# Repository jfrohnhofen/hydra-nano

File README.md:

# hydra nano

**hydra nano** is an open-source, ultra-compact 8-channel sACN (E1.31) lighting output controller. Powered by a Raspberry Pi Pico (RP2040) and a WIZnet W5500 SPI Ethernet module, it drives WS2812B addressable LED strings (via RP2040 PIO state machines) or high-frequency hardware PWM dimmers, configurable via a web interface.

---

## Features

- **8 Independent Output Channels**, each supporting one of the following modes:
  - **WS2812B Pixel Mode**: Up to 1,000 pixels per channel.
  - **WS2812B Uniform Fill Mode**: Controls an entire strip with a single DMX RGB slot triplet.
  - **PWM Dimming**: High-frequency PWM for MOSFET-switched single-color fixtures.
- **sACN Protocol Support**:
  - Listens on multicast and unicast UDP port `5568`.
  - Configurable stream loss behavior per channel: **Hold**, **Blackout**, or timed **Fade**.
- **Robust Networking & Zero-Conf Discovery**:
  - Hardware TCP/IP offload via WIZnet W5500 10/100 Mbps Ethernet.
  - Automatic DHCP with auto-retry.
  - Deterministic fallback link-local IPv4 (`169.254.x.y`) derived from hardware UID.
  - mDNS announcement (`<hostname>.local`, `_http._tcp`, `_hydra_nano._tcp`) and ICMP ping support.
- **Embedded Web Management Server**:
  - Simple responsive web UI on port 80 for live universe stream monitoring, network setup, channel configuration, and interactive test pattern generation.
- **Code-Defined Hardware & Enclosure**:
  - Schematic and netlist defined in atopile code ([`pcb/main.ato`](pcb/main.ato)).
  - Level-shifted outputs (3.3V to 5V) with solder bypass jumpers.
  - Snap-fit 3D CAD enclosure models ([Onshape](https://cad.onshape.com/documents/83539edf775ddacd0b6ac004/w/c1c705bfbe98832503cfb8b5/e/50ee4a9a96b406c057eff376)) with label generator.

---

## Hardware Architecture

### Channel & GPIO Mapping

The 8 physical outputs are ordered West-to-East across the board headers:

| Channel | Label | RP2040 GPIO | PWM Slice / PIO | Level Shifter | Bypass Jumper | Output Connector |
| :---: | :---: | :---: | :---: | :---: | :---: | :---: |
| **Ch 1** | OUT 1 | `GP15` | PWM Slice 7 B / PIO0 SM0 | Shifter `A1` $\rightarrow$ `B1` | `SJ1` | IDC 6-Pin #1 Pin 4 |
| **Ch 2** | OUT 2 | `GP14` | PWM Slice 7 A / PIO0 SM1 | Shifter `A2` $\rightarrow$ `B2` | `SJ2` | IDC 6-Pin #1 Pin 1 |
| **Ch 3** | OUT 3 | `GP13` | PWM Slice 6 B / PIO0 SM2 | Shifter `A3` $\rightarrow$ `B3` | `SJ3` | IDC 10-Pin Pin 7 |
| **Ch 4** | OUT 4 | `GP12` | PWM Slice 6 A / PIO0 SM3 | Shifter `A4` $\rightarrow$ `B4` | `SJ4` | IDC 10-Pin Pin 5 |
| **Ch 5** | OUT 5 | `GP11` | PWM Slice 5 B / PIO1 SM0 | Shifter `A5` $\rightarrow$ `B5` | `SJ5` | IDC 10-Pin Pin 3 |
| **Ch 6** | OUT 6 | `GP10` | PWM Slice 5 A / PIO1 SM1 | Shifter `A6` $\rightarrow$ `B6` | `SJ6` | IDC 10-Pin Pin 1 |
| **Ch 7** | OUT 7 | `GP9` | PWM Slice 4 B / PIO1 SM2 | Shifter `A7` $\rightarrow$ `B7` | `SJ7` | IDC 6-Pin #2 Pin 4 |
| **Ch 8** | OUT 8 | `GP8` | PWM Slice 4 A / PIO1 SM3 | Shifter `A8` $\rightarrow$ `B8` | `SJ8` | IDC 6-Pin #2 Pin 1 |

---

### W5500 Ethernet SPI Wiring

The W5500 module is connected to RP2040 hardware `SPI0`:

| Signal | Pico GPIO | Pico Pin | W5500 Pin | Function |
| :--- | :---: | :---: | :---: | :--- |
| **MISO** | `GP0` | Pin 1 | Pin 12 | SPI0 RX / Master In Slave Out |
| **RSTn** | `GP1` | Pin 2 | Pin 11 | Active-low hardware reset |
| **SCK** | `GP2` | Pin 4 | Pin 4 | SPI0 Clock |
| **MOSI** | `GP3` | Pin 5 | Pin 3 | SPI0 TX / Master Out Slave In |
| **INTn / IRQ**| `GP4` | Pin 6 | Pin 6 | Active-low interrupt line |
| **CSn** | `GP5` | Pin 7 | Pin 5 | Active-low SPI Chip Select |

---

### IDC Headers & Connectors

Outputs are distributed via standard 2.54 mm pitch right-angle shrouded box headers:

- **IDC 6-Pin Header #1**:
  - Pin 1: `Ch 2` (GP14) | Pin 2: `GND` | Pin 3: `5V`
  - Pin 4: `Ch 1` (GP15) | Pin 5: `GND` | Pin 6: `5V`
- **IDC 10-Pin Header**:
  - Odd pins (signals/power): Pin 1: `Ch 6` (GP10), Pin 3: `Ch 5` (GP11), Pin 5: `Ch 4` (GP12), Pin 7: `Ch 3` (GP13), Pin 9: `5V`
  - Even pins: Dedicated ground lines (Pins 2, 4, 6, 8, 10: `GND`)
- **IDC 6-Pin Header #2**:
  - Pin 1: `Ch 8` (GP8) | Pin 2: `GND` | Pin 3: `5V`
  - Pin 4: `Ch 7` (GP9) | Pin 5: `GND` | Pin 6: `5V`

---

## Firmware

The firmware is written in async Rust using the **Embassy** framework.

1. **Core 0 (Networking & Control)**:
   - Manages SPI transactions with the W5500.
   - Parses incoming sACN packets and updates atomic universe double-buffers.
   - Runs the embedded web server, responds to mDNS queries, and monitors DHCP leases.
   - Manages non-volatile flash writes when configuration changes occur.
2. **Core 1 (Real-Time Output Generation)**:
   - Dedicated exclusively to output generation, isolated from network interrupts.
   - Dispatches parallel DMA transfers to PIO0 and PIO1 state machines for 800 kHz WS2812 timing.
   - Updates hardware PWM compare registers and computes flame simulation frames.

## Getting Started & Development

### Environment Setup (Nix Flake)

The repository provides reproducible Nix development shells for both PCB design and firmware development:

```bash
# Enter the firmware dev shell (Rust toolchain, picotool, defmt-print, probe-rs)
nix develop .#firmware

# Enter the PCB dev shell (atopile, KiCad 10, librsvg)
nix develop .#pcb

# Or if using direnv:
direnv allow
```

---

### Firmware Development & Flashing

Within `firmware/` or inside the `.#firmware` shell:

```bash
# 1. Run host-side unit tests
cargo test -p sacn-core

# 2. Check embedded firmware target
cargo fw-check

# 3. Build release binary for RP2040
cargo fw-build

# 4. Flash over USB and automatically stream defmt logs
cargo fw-run

# 5. Flash via debug probe (e.g. Raspberry Pi Debug Probe / CMSIS-DAP)
cargo fw-run-probe

# 6. Preview the embedded Web UI in your desktop browser
cargo web-preview
```

#### Flashing Workflow (`fw-flash`)

The [`scripts/fw-flash`](firmware/scripts/fw-flash) script handles USB flashing without requiring physical access to the BOOTSEL button:
1. Reboots the board into the RP2040 ROM bootloader over USB serial (1200 baud pulse).
2. Erases the non-volatile configuration flash sector (`0x101FF000`) to guarantee fresh defaults (override with `FW_KEEP_CONFIG=1`).
3. Loads the ELF binary via `picotool`.
4. Spawns [`scripts/fw-logs`](firmware/scripts/fw-logs) to decode and stream structured `defmt` logs over USB CDC serial.

---

### PCB Build & EDA Workflow

The PCB is defined in atopile code ([`pcb/main.ato`](pcb/main.ato)) and laid out in KiCad ([`pcb/layouts/hydra-nano`](pcb/layouts/hydra-nano)):

```bash
# Enter PCB shell
nix develop .#pcb

cd pcb

# Build KiCad netlist and manufacturing files
ato build

# Validate frozen layout in CI
ato build --frozen

# Open PCB layout in KiCad
kicad layouts/hydra-nano/hydra-nano.kicad_pcb
```

---

## Web Configuration UI

Each hydra nano unit hosts an embedded web server accessible via standard web browsers:

1. Connect the board to your local network via an Ethernet cable.
2. In your browser, navigate to:
   ```
   http://<hostname>.local/
   ```
   *(e.g., `http://hydra-3a4b5c.local/` or the assigned DHCP / fallback IP address)*.

### Web UI Features
- **Dashboard**: Live stream reception rates, dropped packets, network link status, and unit temperature.
- **Channel Configuration**:
  - Select mode per channel (`WS2812`, `WS2812 Fill`, `PWM`, `Fire`, or `Off`).
  - Configure sACN universe assignment and starting DMX address.
  - Set pixel count.
  - Set loss-of-signal behavior (**Hold**, **Blackout**, or **Fade**).
- **Network Settings**: Toggle DHCP vs. Static IP, subnet mask, and hostname.
- **Test Pattern Generator**: Trigger solid colors, rainbow sweeps, or alternating chase patterns directly from the browser without sending external DMX data.

---

## Enclosure & Production Labels

The [`enclosure/`](enclosure) directory contains mechanical files and automated labeling tools:
- **Onshape CAD Document**: [hydra-nano on Onshape](https://cad.onshape.com/documents/83539edf775ddacd0b6ac004/w/c1c705bfbe98832503cfb8b5/e/50ee4a9a96b406c057eff376)
- **3D Models**: Exported STEP files for the enclosure halves are available in [`enclosure/`](enclosure).
- **Automated Label Sheet Generator ([`make_labels.py`](enclosure/make_labels.py))**:
  Generates production-ready, calibrated PDF label sheets (A4 or US Letter) with crop marks and BOOTSEL hole punch markers from a CSV list of units:

  ```bash
  # Generate labels from a CSV list of MAC addresses and hostnames
  ./enclosure/make_labels.py units.csv -o labels.pdf --copies 3 --paper a4
  ```

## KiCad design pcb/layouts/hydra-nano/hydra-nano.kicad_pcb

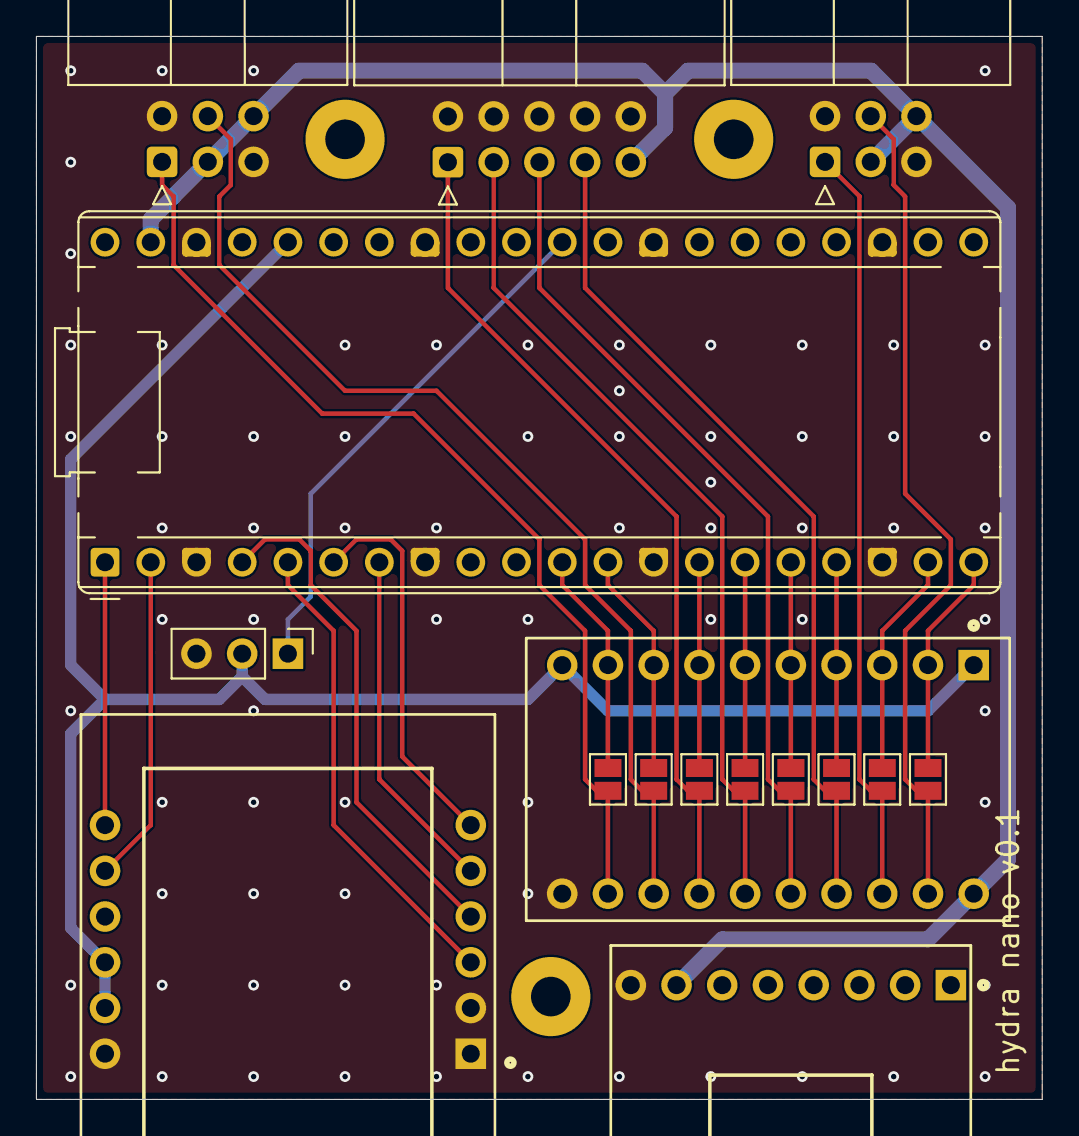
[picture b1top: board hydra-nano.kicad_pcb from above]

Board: 2 copper layers, 55.9 x 59.1 mm, 19 parts (0 on the bottom side), 26 nets.

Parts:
U1: W5500_Module_2x06_P2.54mm_W20.32mm
U2: RaspberryPi_Pico_Common_THT
U3: USBC_Breakout_8Pin_20x14mm
U4, U5: IDC-Header_2x03_P2.54mm_Horizontal
U6: IDC-Header_2x05_P2.54mm_Horizontal
U7, U9, U10, U11, U12, U13, U14, U15: SolderJumper-2_P1.27mm_Open_Pad1.0x1.5mm
U8: Module_LevelShifter_2x10_P2.54mm_W12.7mm
U16: PinHeader_1x03_P2.54mm_Vertical
U17, U18, U19: MountingHole_2.2mm_M2_Pad

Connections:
GND: U1.1, U1.2, U1.7, U2.3, U2.8, U2.13, U2.18, U2.23, U2.28, U2.33, U2.38, U3.8, U4.2, U4.5, U5.2, U5.5, U6.2, U6.4, U6.6, U6.8, U6.10, U8.11, U16.3
MISO: U1.12, U2.1
MOSI: U1.3, U2.5
SCLK: U1.4, U2.4
a1: U2.20, U7.1, U8.2
a2: U2.19, U8.3, U9.1
a3: U2.17, U8.4, U10.1
a4: U2.16, U8.5, U11.1
a5: U2.15, U8.6, U12.1
a6: U2.14, U8.7, U13.1
a7: U2.12, U8.8, U14.1
a8: U2.11, U8.9, U15.1
b3: U6.7, U8.17, U10.2
b4: U6.5, U8.16, U11.2
b5: U6.3, U8.15, U12.2
b6: U6.1, U8.14, U13.2
footprint-gpio_a-0: U4.1, U8.18, U9.2
footprint-gpio_a-1: U5.1, U8.12, U15.2
footprint-gpio_b-0: U4.4, U7.2, U8.19
footprint-gpio_b-1: U5.4, U8.13, U14.2
gp1: U1.11, U2.2
gp4: U1.6, U2.6
gp5: U1.5, U2.7
power-VCC: U2.39, U3.7, U4.3, U4.6, U5.3, U5.6, U6.9, U8.20
power_3v3-VCC: U1.8, U1.9, U2.36, U8.1, U8.10, U16.2
rst: U2.30, U16.1

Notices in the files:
README.md:
License: MIT
